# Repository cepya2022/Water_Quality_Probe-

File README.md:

# Water_Quality_Probe-

## Introduction

The development of open-source code and hardware instruments enables both the creation of new technologies and the redesign and adaptation of existing instruments to the user's specific needs. This allows free access to design and operational documentation, creating the possibility for the developed instruments to be replicated, assembled, studied, modified, shared, and collaboratively commercialized by anyone.

The current project involves the design of a low-cost multiparametric water quality probe that enables in situ and remote sensing of physicochemical variables relevant to the environment, such as conductivity, dissolved oxygen, temperature, and pH in bodies of water. The first prototype based on Arduino is already available, and efforts are underway to refine it in order to achieve a more robust, economical, and efficient product. This project proposes integrating the microcontroller into a single printed circuit board (PCB) that facilitates data acquisition and storage over extended periods, reduces energy consumption, and enhances robustness, considering its predominantly outdoor operation.

### Hardware

The monitoring station consists of a sealed waterproof box that floats with the assistance of auxiliary buoys. Inside the box, there is an Arduino Mega microcontroller connected to an external clock, an SD memory module, a low-energy Bluetooth module, a solar-powered energy system, and signal processing and decoupling systems for each sensor. Submersible cables extend from this box to the probes, allowing sampling in the water.

Regarding energy aspects, a solar-powered system was designed. It includes a Li-Ion battery (or two arranged in parallel) that powers the microcontroller and sensors, connected to a 1 Watt solar panel, providing indefinite energy autonomy.

Additionally, it integrates a Bluetooth device using 4.0 BLE (Bluetooth Low Energy) technology. The Serial Bluetooth Terminal® app enables remote control of the probe, such as remote power on/off, selection of measurement intervals, sensor calibration, and data query, curing, and collection. It's worth noting that each measurement includes the exact date and time it was taken. These features make it easy to remotely monitor many relevant variables over extended periods with high sampling rates, allowing for detailed time-series data collection at the study site.

#### Components

* Solar Panel
* Double battery holder
* Arduino Mega 2560 Rev3
* Step Up Power Supply Xl6009 Dc Adjustable Dc 5v 35v 3a Max Arduino
* Lithium Battery Charger Micro USB Module Tp4056 5v
* HC-08 BLE Bluetooth Module
* Micro SD Memory Reader Module: hw-125
* DS3231 RTC Clock
* DS18B20 Submersible Stainless Steel Digital Temperature Sensor
* PH-4502C Liquid PH Sensor with E201-BNC Electrode
* Conductivity Sensor Conductivity K 1.0 Kit (Atlas Scientific)
* Gravity™ Analog Dissolved Oxygen Meter Dissolved Oxygen Sensor (Atlas Scientific)
* 6x 2N7000 N-Channel MOSFETs (low-side power switching, one per module)
* Resistors (1 kΩ gate series, 220 kΩ gate pull-down, 1.7 kΩ OneWire pull-up)

Each sensor and peripheral (pH, conductivity, dissolved oxygen, temperature, RTC and SD card) has
its ground routed through its own 2N7000 MOSFET, so the microcontroller can power each module
independently. Driving the corresponding gate pin `HIGH` closes the low-side switch and powers the
module; `LOW` removes its ground reference and turns it off. Earlier prototypes used an
optocoupled relay module for this; the V1.0 PCB replaced it entirely with MOSFETs.

### Software

The research team is continuosly working on and improving the code. It is written in c++ programming language inside the Arduino IDE as it is the default language for arduino microcontrollers. The system was design to enter sleep mode inside the loop function while the `measurement` option is disabled or in between measurements. It includes an interruption function which is activated once a message is received via Bluetooth. This function wakes the system, executes the corresponding command and once it is finished, it enters the loop again. The different commands include turning on/off the measurement cycle and setting its frequency, sensor calibration, data query and current state information. The updated code is available [here](https://github.com/cepya2022/Water_Quality_Probe-/blob/main/Code_Water_Quality_Probe.ino).

#### Building the firmware

Target board: **Arduino Mega 2560**.

⚠️ **`do_grav.h` is not included in this repository**, so the sketch will not compile from a fresh
clone until the library that provides it is installed. It comes from Atlas Scientific's
**`atlas_gravity`** library (the `Gravity_DO` class used for the dissolved oxygen sensor). That
library is not published to the Arduino Library Manager — download it from Atlas Scientific's
GitHub and copy the `atlas_gravity` folder into your Arduino `libraries/` directory manually.

The following libraries are also required. All except `atlas_gravity` are available through the
Arduino IDE Library Manager:

| Library | Used for |
|---|---|
| `atlas_gravity` | dissolved oxygen sensor (`do_grav.h`) — **manual install, see above** |
| `RTClib` | DS3231 real time clock |
| `Low-Power` | sleep between measurements |
| `DallasTemperature` | DS18B20 temperature sensor |
| `OneWire` | DS18B20 bus |
| `Wire` | I²C (RTC) — bundled with the IDE |
| `SPI` | SD card bus — bundled with the IDE |
| `SD` | SD card — bundled with the IDE |

The conductivity module is driven over `Serial2` with plain text commands, so it needs no library.

Setting the clock: `corregirReloj()` is called from `setup()` but is left commented out. Uncomment
it, upload once while connected to a computer so the RTC picks up the compile-time timestamp, then
comment it out again and re-upload — otherwise the clock is reset to the compile time on every boot.

#### Measurement cycles

Once the measurment is set to `On`, the interface will ask the user to identify the location with an ID (`locationID`) which must be a number. Once it is provided, the arduino will save the `On` state along with the location ID and the current frequency (default is 15 seconds), in a .txt file inside the SD Card. This feature acts as a reassurance in case of a sudden shutdown and restart of the system or any kind of reboot. In this case, during the setup function of the arduino, this file is checked to seek the last state in which the system was operating. In case the measurement was `On`, it sets the frequency and the location ID to their previous states and starts the measurement cycle, otherwise it keeps the default values and enters the loop. The frequency intervals available in the current version are 15 seconds and 1, 5, 15 or 30 minutes. Usually, for outdoor measurements, 30 minutes is a reasonable interval considering battery consumption, solar exposure and a relatively high sampling rate compared to other sampling methods.

During the measurement cycle, the arduino powers each sensor on and off in turn, so that only the module being read draws current at any given moment. First it turns on the pH sensor (`pH`) and waits about 2 seconds for it to settle, then averages 10 consecutive analog samples taken 10 ms apart and converts that average to a pH value using the stored calibration line. Next is the temperature sensor (`T`), which is read once. Third is the conductivity sensor (`EC`), one of the most accurate and precise ones and the slowest per reading, so a single measurement is taken; the value returned by the module is temperature-compensated, which is why it must be read after the temperature. Along with conductivity, the module also returns total dissolved solids (`TDS`). Finally, the dissolved oxygen (`DO`) is read once. Once the parameters are measured, the current date and time are read from the RTC and the record is appended to a .txt file on the SD card as semicolon-separated values, in the order: `date`;`time`;`DO`;`EC`;`TDS`;`pH`;`T`;`locationID`.

> Note: earlier revisions of this document described a 3 minute pH stabilization wait, attributed to
> induction from the relay module, and a 10-reading average for every sensor. Both belong to the
> relay-based prototype and do not describe the current firmware — the V1.0 board has no relays, and
> only pH averages multiple samples. The paragraph above reflects what the code actually does.

#### Data query and state info

There are 3 types of data querys available. The first to refer to the data stored from the measurement cycles. One of them returns the entire information stored in the SD card inside the measurement file, while the other returns only the new information added since the last measurement data query. In case of a shutdown and restart of the system or any kind of reboot, the pointer of the file returns to the first line of the text file, so both queries will return the same information. The third type of data query refers to individual measurements of each sensor taken at real-time. This includes options for each of the 4 sensors and the RTC clock.

The current state information is also a query that returns wether the the measurement mode is On or Off, and the established frequency.

#### Sensor Calibration

The only sensor without the need of a calibration process is the Temperature one, the other three sensors have specific code and procedures for their correct calibrations. 

For the pH sensor, the calibration requires a pH=7 and a pH=4 standard solutions. First, the interface will request the user to use the pH=7 solution and press the `Ok` command when a stable condition is reached. It is recommended to wait at least 3 minutes until it reaches a stable electronic condition in each solution. Then, it will request to do the same in the pH=4 solution. Make sure to wash the probe with distilled water in between solutions. Once both solutions are used, the arduino will give the user the notification that the pH sensor is calibrated and it will save the calibration curve parameters, slope of curve (m) and intercept to the origin (O.o.), in the same file as the Location ID and the measurement state for it to be used in case of a sudden shutdown and restart of the system or any kind of reboot.

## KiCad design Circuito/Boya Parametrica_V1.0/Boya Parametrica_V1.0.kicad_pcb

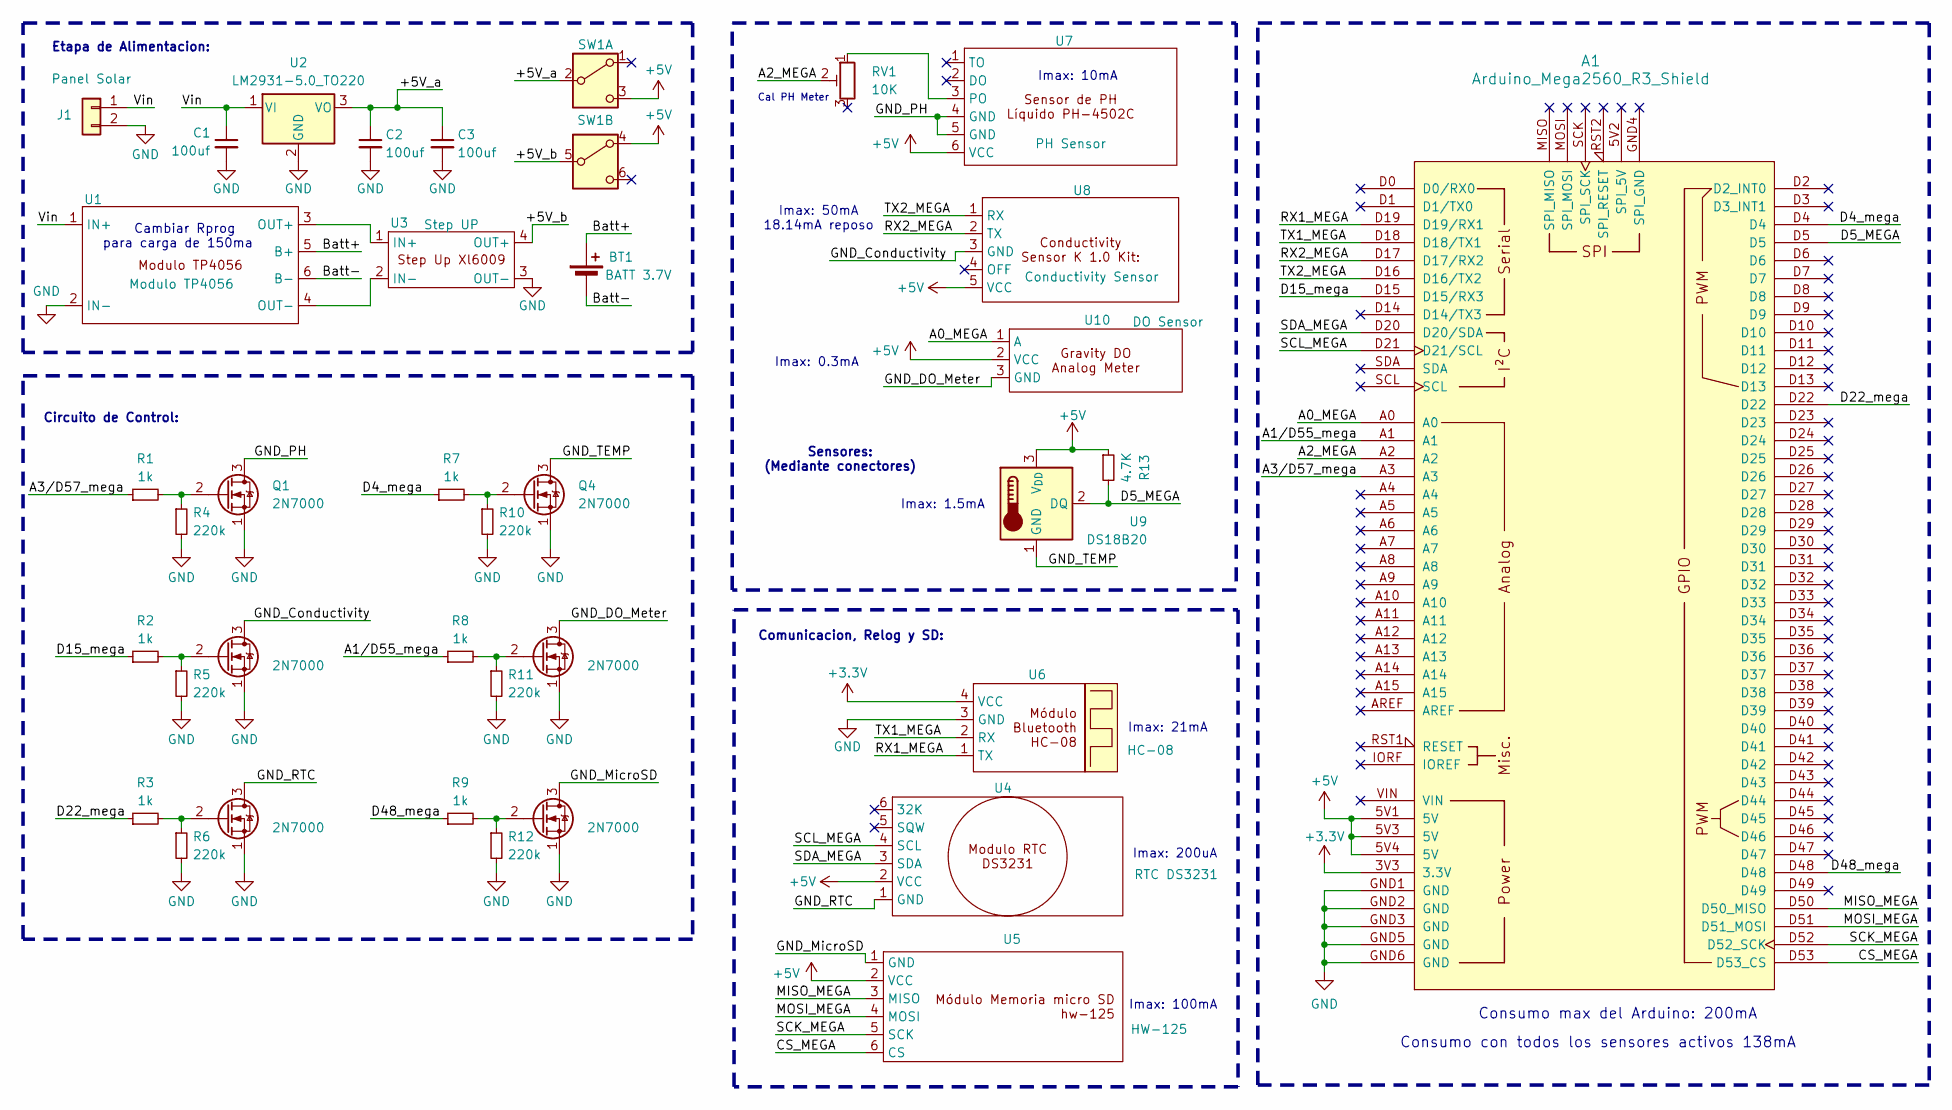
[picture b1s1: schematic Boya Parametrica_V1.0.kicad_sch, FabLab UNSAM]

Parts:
A1: Arduino_Mega2560_R3_Shield
BT1: BATT 3.7V; JST_EH_B2B-EH-A_1x02_P2.50mm_Vertical
C1, C2, C3: 100uf; C_Disc_D3.8mm_W2.6mm_P2.50mm
J1: Panel Solar; TerminalBlock_bornier-2_P5.08mm
Q1, Q2, Q3, Q4, Q5, Q6: 2N7000; TO-92L_Wide
R1, R2, R3, R7, R8, R9: 1k; R_Axial_DIN0204_L3.6mm_D1.6mm_P5.08mm_Horizontal
R4, R5, R6, R10, R11, R12: 220k; R_Axial_DIN0204_L3.6mm_D1.6mm_P5.08mm_Horizontal
R13: 4.7K; R_Axial_DIN0204_L3.6mm_D1.6mm_P5.08mm_Horizontal
RV1: 10K; Potentiometer_Bourns_3296W_Vertical
SW1: SW_CK_JS202011AQN_DPDT_Angled
U1: Modulo TP4056; TP4056-18650
U2: LM2931-5.0_TO220; TO-220-3_Vertical
U3: Step UP; hw-045
U4: RTC DS3231; RTC_DS3231
U5: HW-125; MICRO SD CARD HW-125
U6: HC-08; JST_EH_B4B-EH-A_1x04_P2.50mm_Vertical
U7: PH Sensor; JST_EH_B6B-EH-A_1x06_P2.50mm_Vertical
U8: Conductivity Sensor; JST_EH_B5B-EH-A_1x05_P2.50mm_Vertical
U9: DS18B20; JST_EH_B3B-EH-A_1x03_P2.50mm_Vertical
U10: DO Sensor; JST_EH_B3B-EH-A_1x03_P2.50mm_Vertical

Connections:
+3.3V: A1.3V3 (3.3V), U6.4 (VCC)
+5V: A1.5V1 (5V), A1.5V3 (5V), A1.5V4 (5V), R13.1, SW1.3 (C), SW1.4 (A), U4.2 (VCC), U5.2 (VCC), U7.6 (VCC), U8.5 (VCC), U9.3 (V_{DD}), U10.2 (VCC)
/+5V_a: C2.1, C3.1, SW1.2 (B), U2.3 (VO)
/+5V_b: SW1.5 (B), U3.4 (OUT+)
/A0_MEGA: A1.A0, U10.1 (A)
/A1/D55_mega: A1.A1, R8.1
/A2_MEGA: A1.A2, RV1.2
/A3/D57_mega: A1.A3, R1.1
/Batt+: BT1.1 (+), U1.5 (B+)
/Batt-: BT1.2 (-), U1.6 (B-)
/CS_MEGA: A1.D53 (D53_CS), U5.6 (CS)
/D4_mega: A1.D4, R7.1
/D5_MEGA: A1.D5, R13.2, U9.2 (DQ)
/D15_mega: A1.D15 (D15/RX3), R2.1
/D22_mega: A1.D22, R3.1
/D48_mega: A1.D48, R9.1
/GND_Conductivity: Q2.3 (D), U8.3 (GND)
/GND_DO_Meter: Q5.3 (D), U10.3 (GND)
/GND_MicroSD: Q6.3 (D), U5.1 (GND)
/GND_PH: Q1.3 (D), U7.4 (GND), U7.5 (GND)
/GND_RTC: Q3.3 (D), U4.1 (GND)
/GND_TEMP: Q4.3 (D), U9.1 (GND)
/MISO_MEGA: A1.D50 (D50_MISO), U5.3 (MISO)
/MOSI_MEGA: A1.D51 (D51_MOSI), U5.4 (MOSI)
/RX1_MEGA: A1.D19 (D19/RX1), U6.1 (TX)
/RX2_MEGA: A1.D17 (D17/RX2), U8.2 (TX)
/SCK_MEGA: A1.D52 (D52_SCK), U5.5 (SCK)
/SCL_MEGA: A1.D21 (D21/SCL), U4.4 (SCL)
/SDA_MEGA: A1.D20 (D20/SDA), U4.3 (SDA)
/TX1_MEGA: A1.D18 (D18/TX1), U6.2 (RX)
/TX2_MEGA: A1.D16 (D16/TX2), U8.1 (RX)
/Vin: C1.1, J1.1, U1.1 (IN+), U2.1 (VI)
GND: A1.GND1 (GND), A1.GND2 (GND), A1.GND3 (GND), A1.GND5 (GND), A1.GND6 (GND), C1.2, C2.2, C3.2, J1.2, Q1.1 (S), Q2.1 (S), Q3.1 (S), Q4.1 (S), Q5.1 (S), Q6.1 (S), R4.2, R5.2, R6.2, R10.2, R11.2, R12.2, U1.2 (IN-), U2.2 (GND), U3.3 (OUT-), U6.3 (GND)
unnamed: Q1.2 (G), R1.2, R4.1
unnamed: Q2.2 (G), R2.2, R5.1
unnamed: Q3.2 (G), R3.2, R6.1
unnamed: Q4.2 (G), R7.2, R10.1
unnamed: Q5.2 (G), R8.2, R11.1
unnamed: Q6.2 (G), R9.2, R12.1
unnamed: U1.3 (OUT+), U3.1 (IN+)
unnamed: U1.4 (OUT-), U3.2 (IN-)
unnamed: RV1.1, U7.3 (PO)

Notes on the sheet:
Circuito de Control:
Sensores: (Mediante conectores)
Imax: 0.3mA
Consumo con todos los sensores activos 138mA
Imax: 1.5mA
Consumo max del Arduino: 200mA
Imax: 21mA
Imax: 10mA
Etapa de Alimentacion:
Imax: 100mA
Imax: 50mA 18.14mA reposo
Cal PH Meter
Imax: 200uA
Comunicacion, Relog y SD:
Cambiar Rprog para carga de 150ma

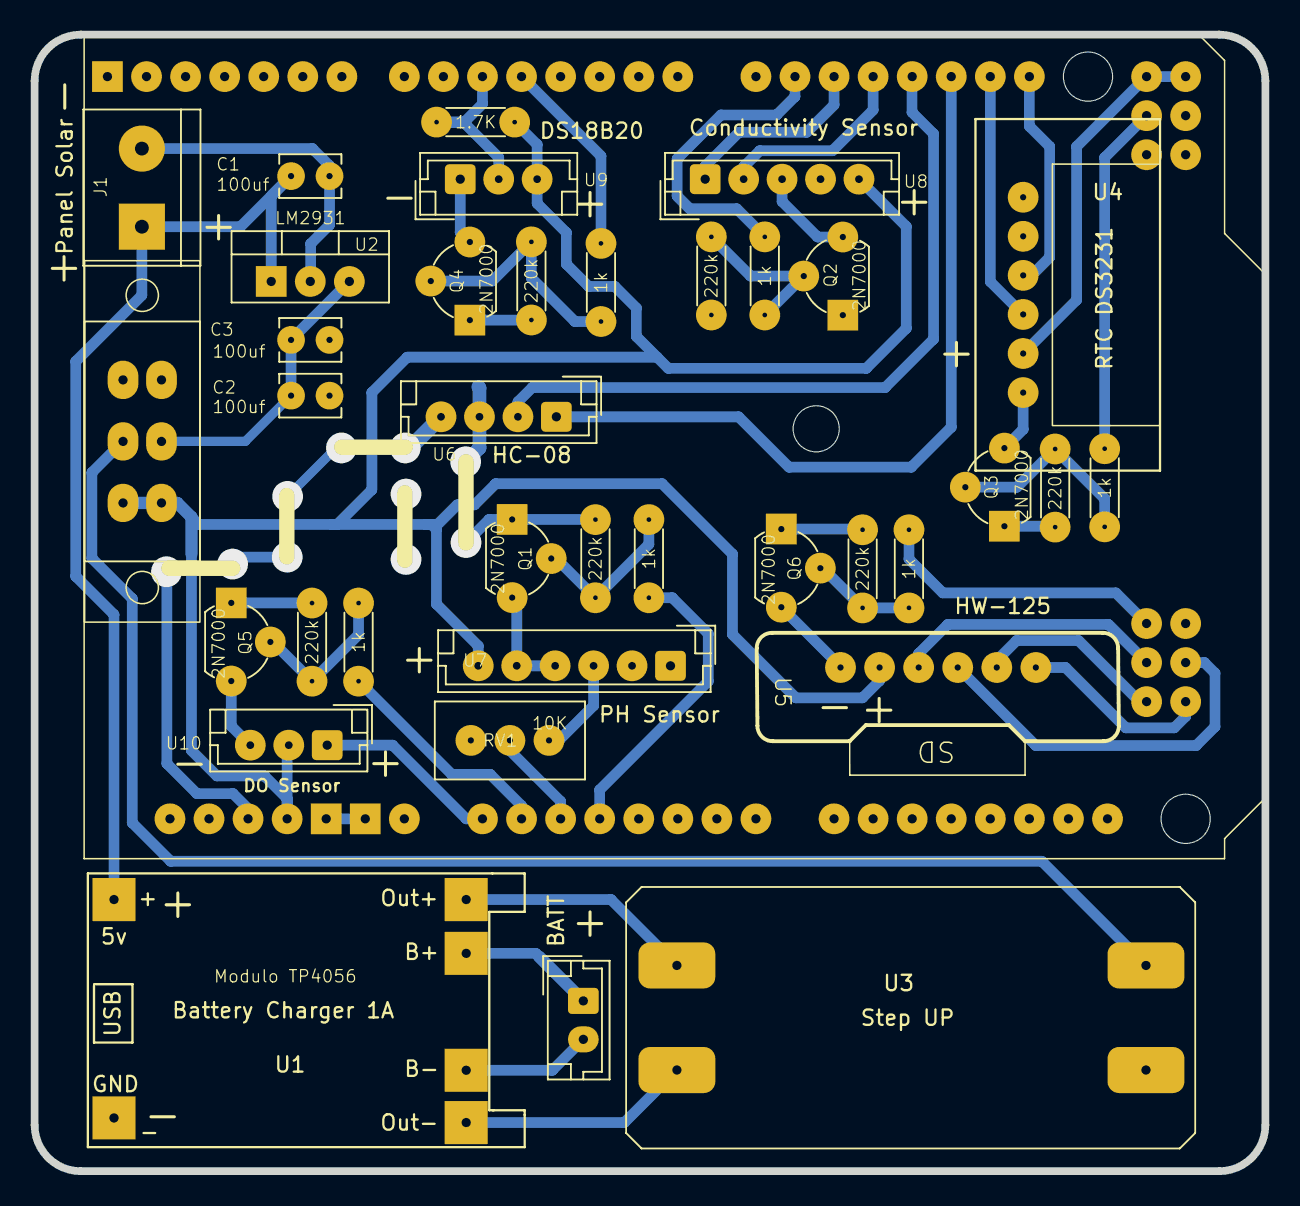
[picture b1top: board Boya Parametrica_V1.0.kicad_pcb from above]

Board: 2 copper layers, 80.0 x 73.9 mm, 37 parts (0 on the bottom side), 42 nets.

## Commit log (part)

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2022-12-15 Update Code_Water_Quality_Probe.ino
    agregue un loop
2023-11-09 Add files via upload
    V23_relay
2023-11-09 First schematic
2024-02-23 Updated code with improvements
2024-02-24 Update main code
2024-02-24 Fixed frequency at restart
2025-12-14 Add files via upload
    Adding Fablab's PCB version 1.0
2025-12-14 Create flutter-app
2025-12-14 Added new flutter app - version 1.0
2025-12-14 Add macos folder
2025-12-14 Add lib folder
2025-12-14 Add ios folder
2025-12-14 Add assets folder
2025-12-14 Add android folder
2025-12-14 Add .idea folder
2025-12-14 Add build folder - loose files
2025-12-15 Finish adding flutter app
2025-12-15 Deleted flutter-app content
2025-12-15 Add flutter-app
2025-12-15 Moved flutter-app up one level
2026-01-07 Changed Logos for android
2026-01-07 changed .csv file export name
2026-01-08 Updated graphs axis labels
2026-01-08 Hide debug flag
